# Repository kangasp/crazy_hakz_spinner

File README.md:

# crazy_hakz_spinner
Spinning LEDs

### Notes from 2-24-23
--------------------------------------------
The footprint for the through beam sensor is wrong - pins 3 and 4 should be switched.
Pin 4 is actually ground / emiter, and pin 3 is actually the collector / vcc.

The through beem should sensor should not be pulled up to VCC - which is 5v.  It should 
be pulled up to 3.3v.

The level shifter should be moved - as it's too close to the mounting bracket... maybe get a bigger one.

Consider moving the positional / counter through beam to the edge.

Consider adding a testpoint header.

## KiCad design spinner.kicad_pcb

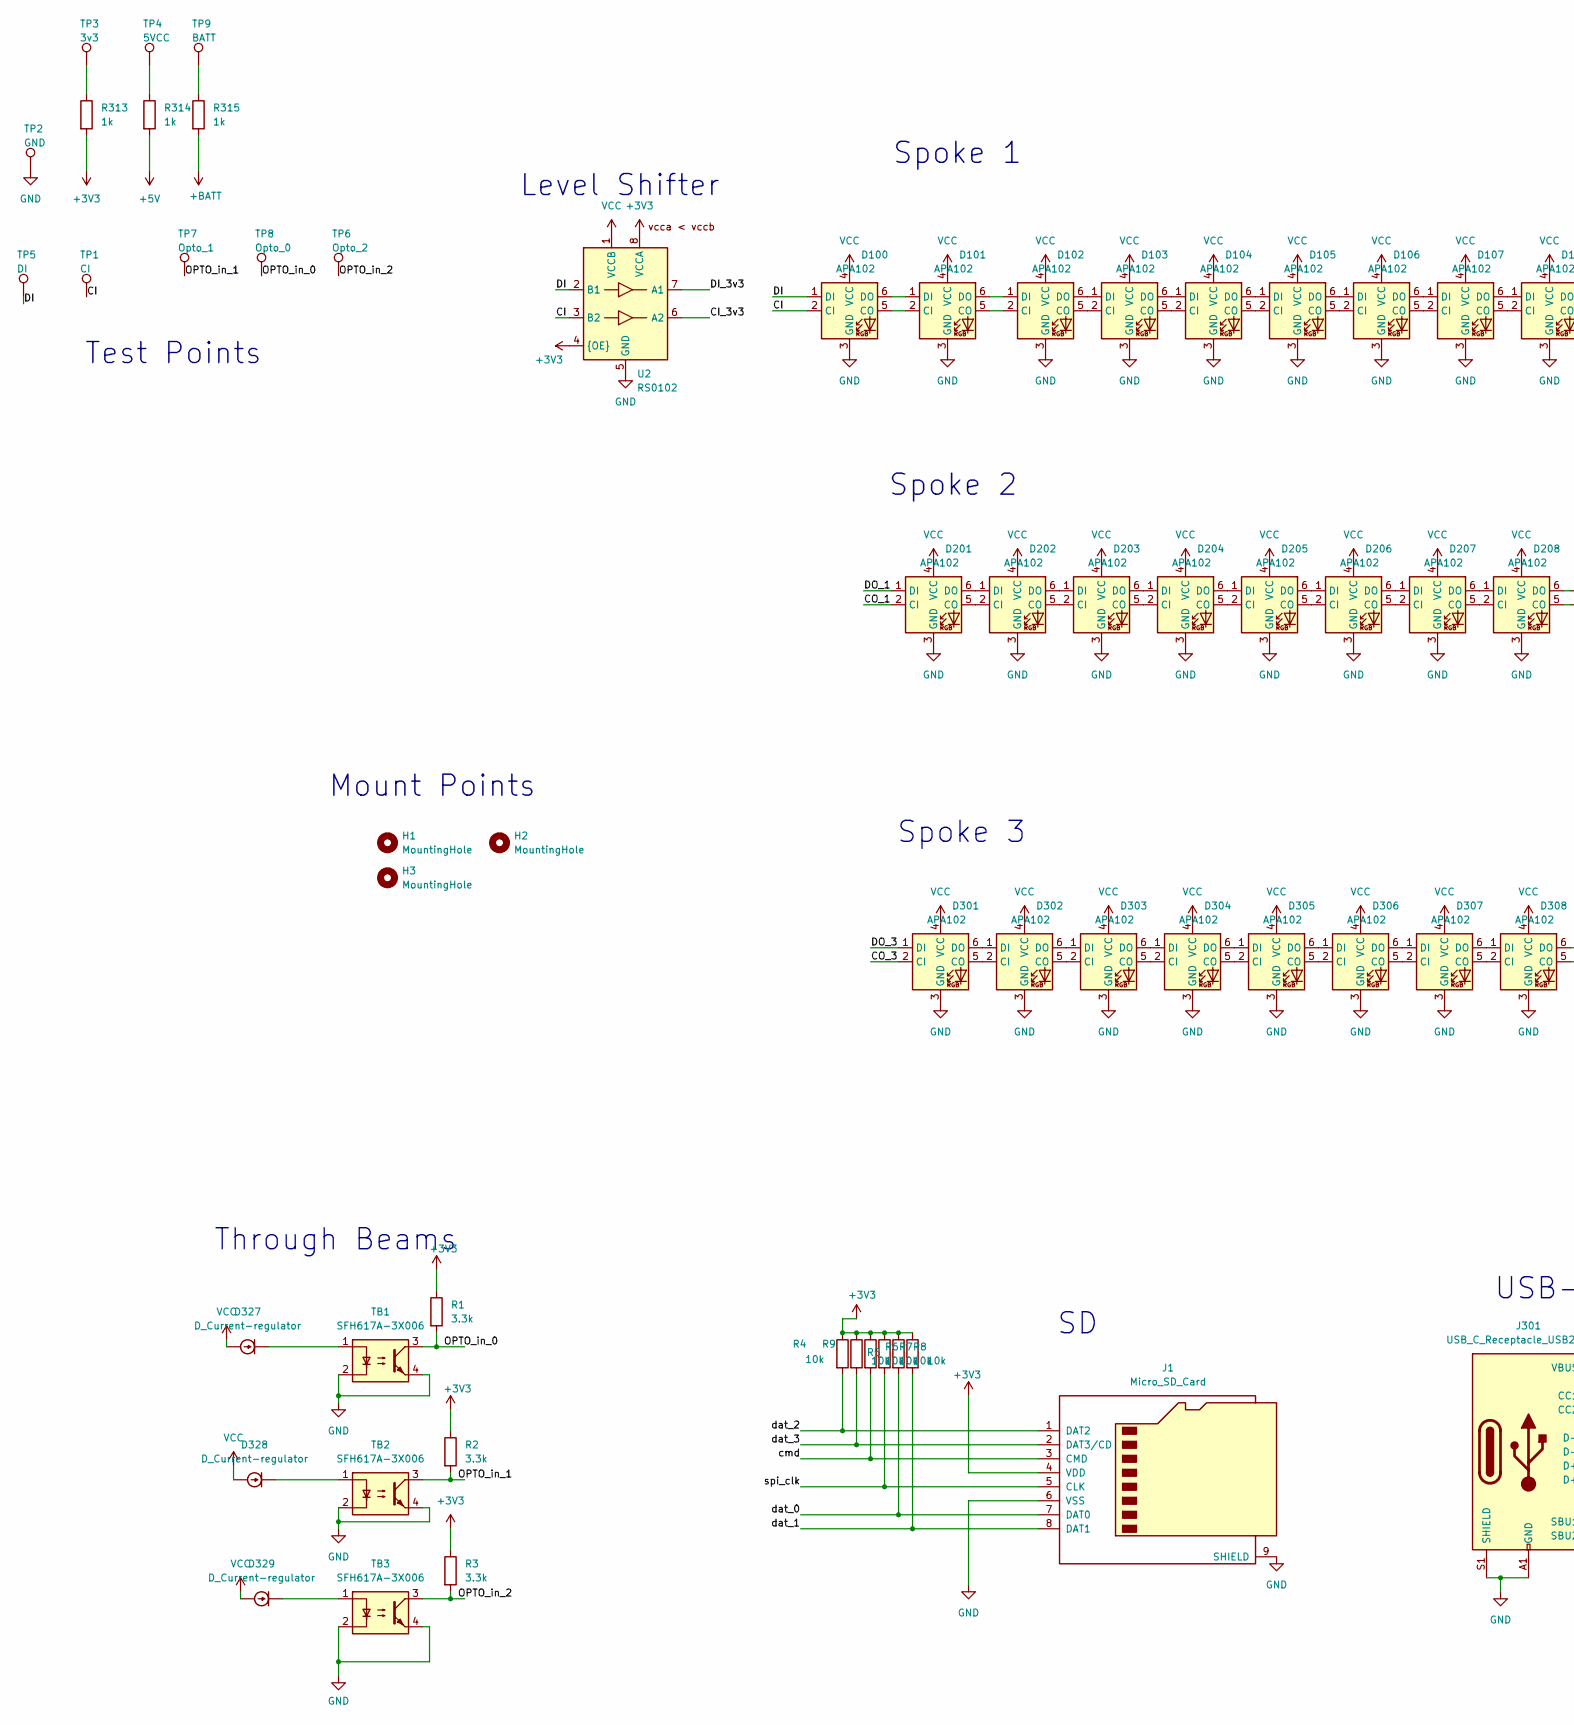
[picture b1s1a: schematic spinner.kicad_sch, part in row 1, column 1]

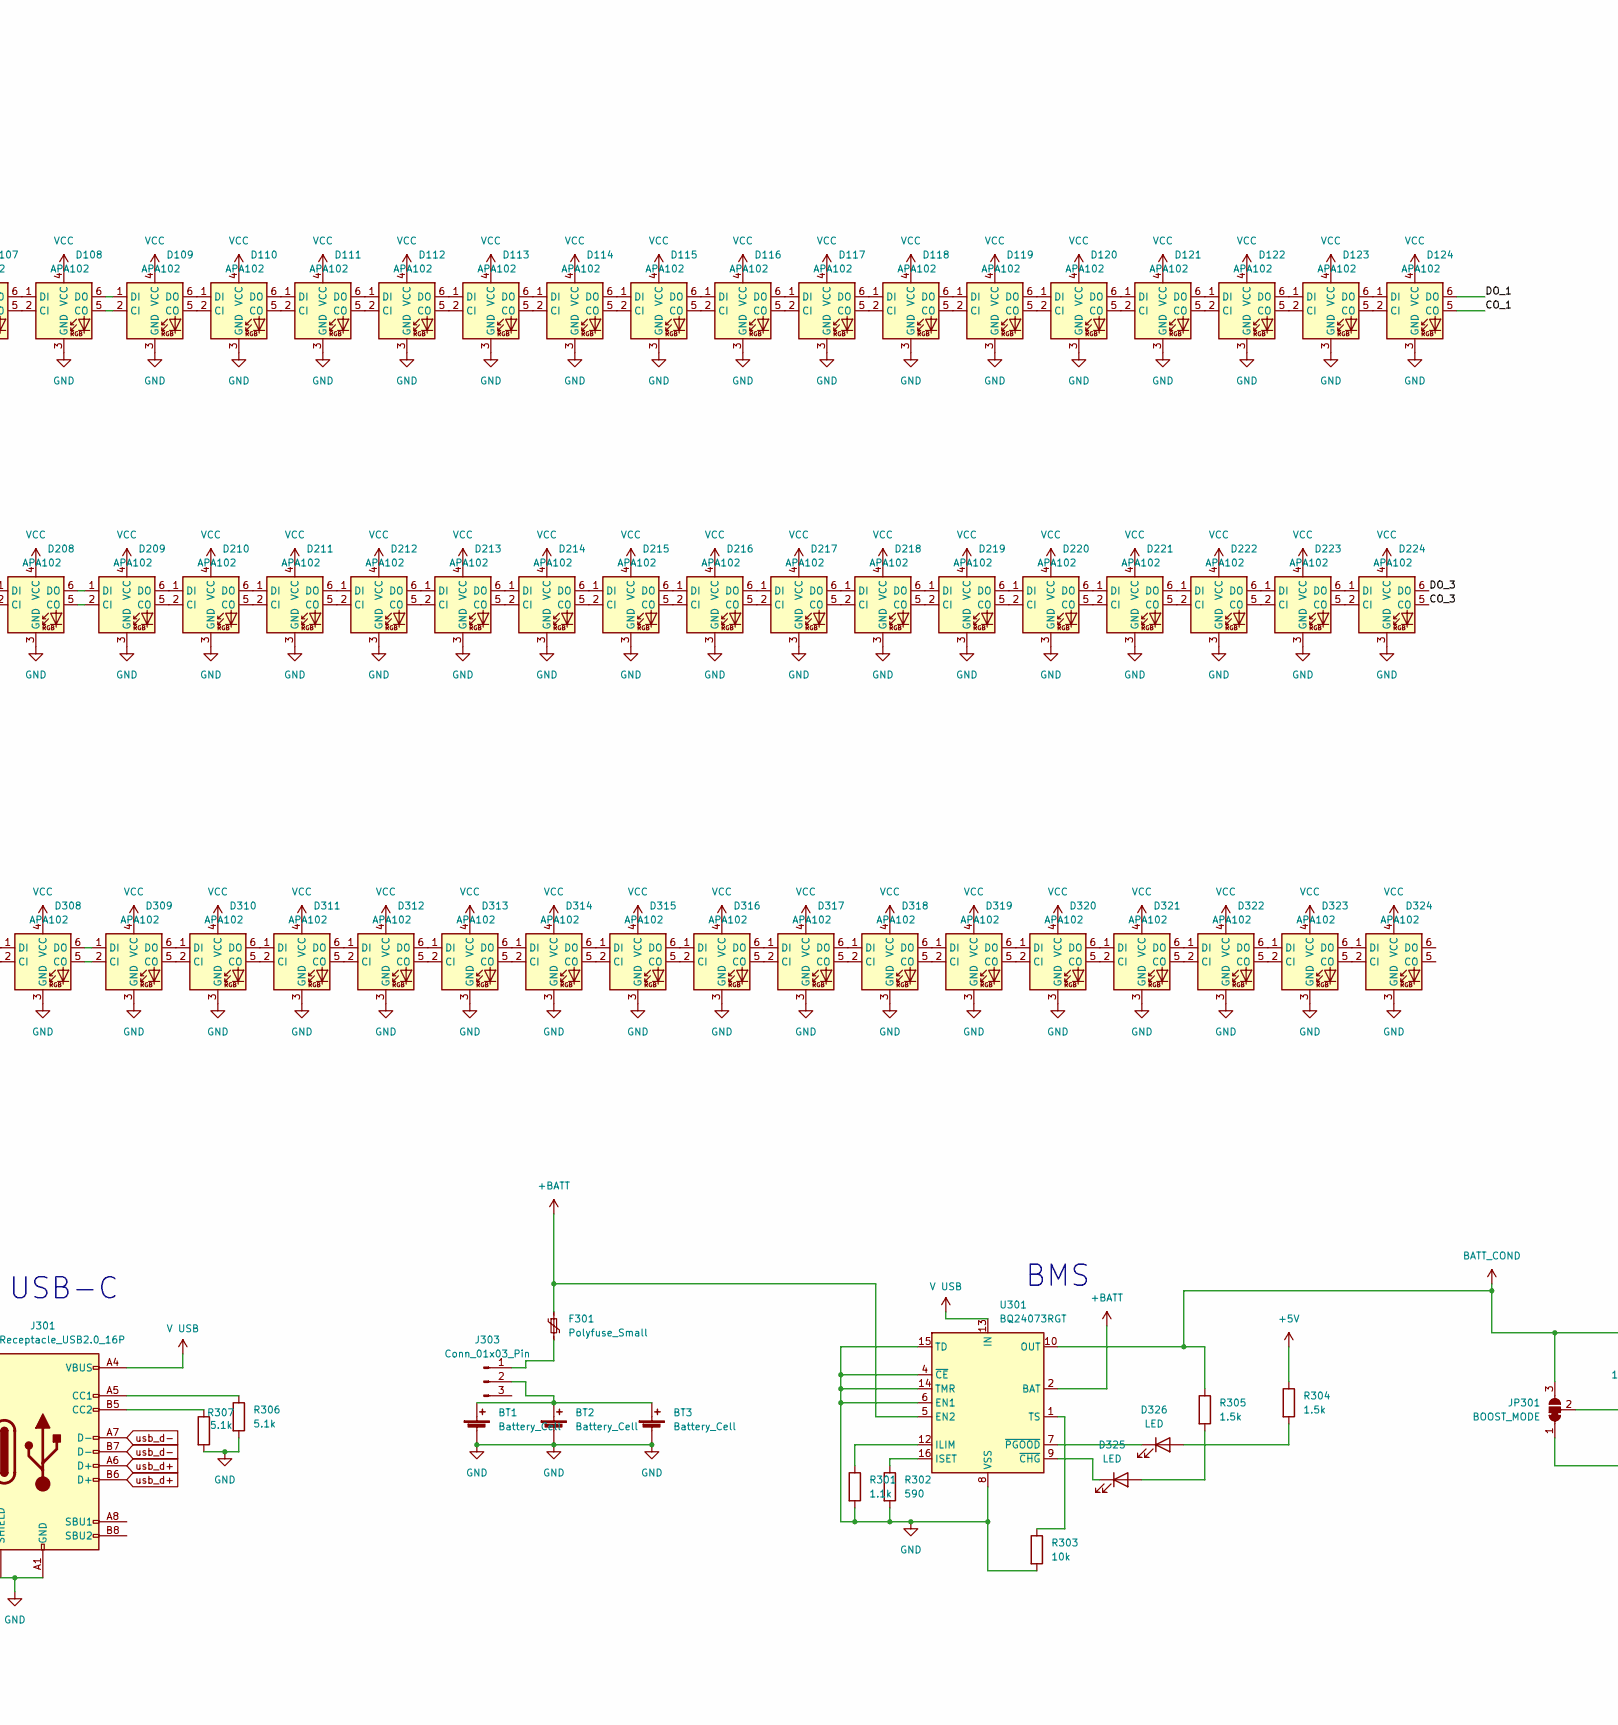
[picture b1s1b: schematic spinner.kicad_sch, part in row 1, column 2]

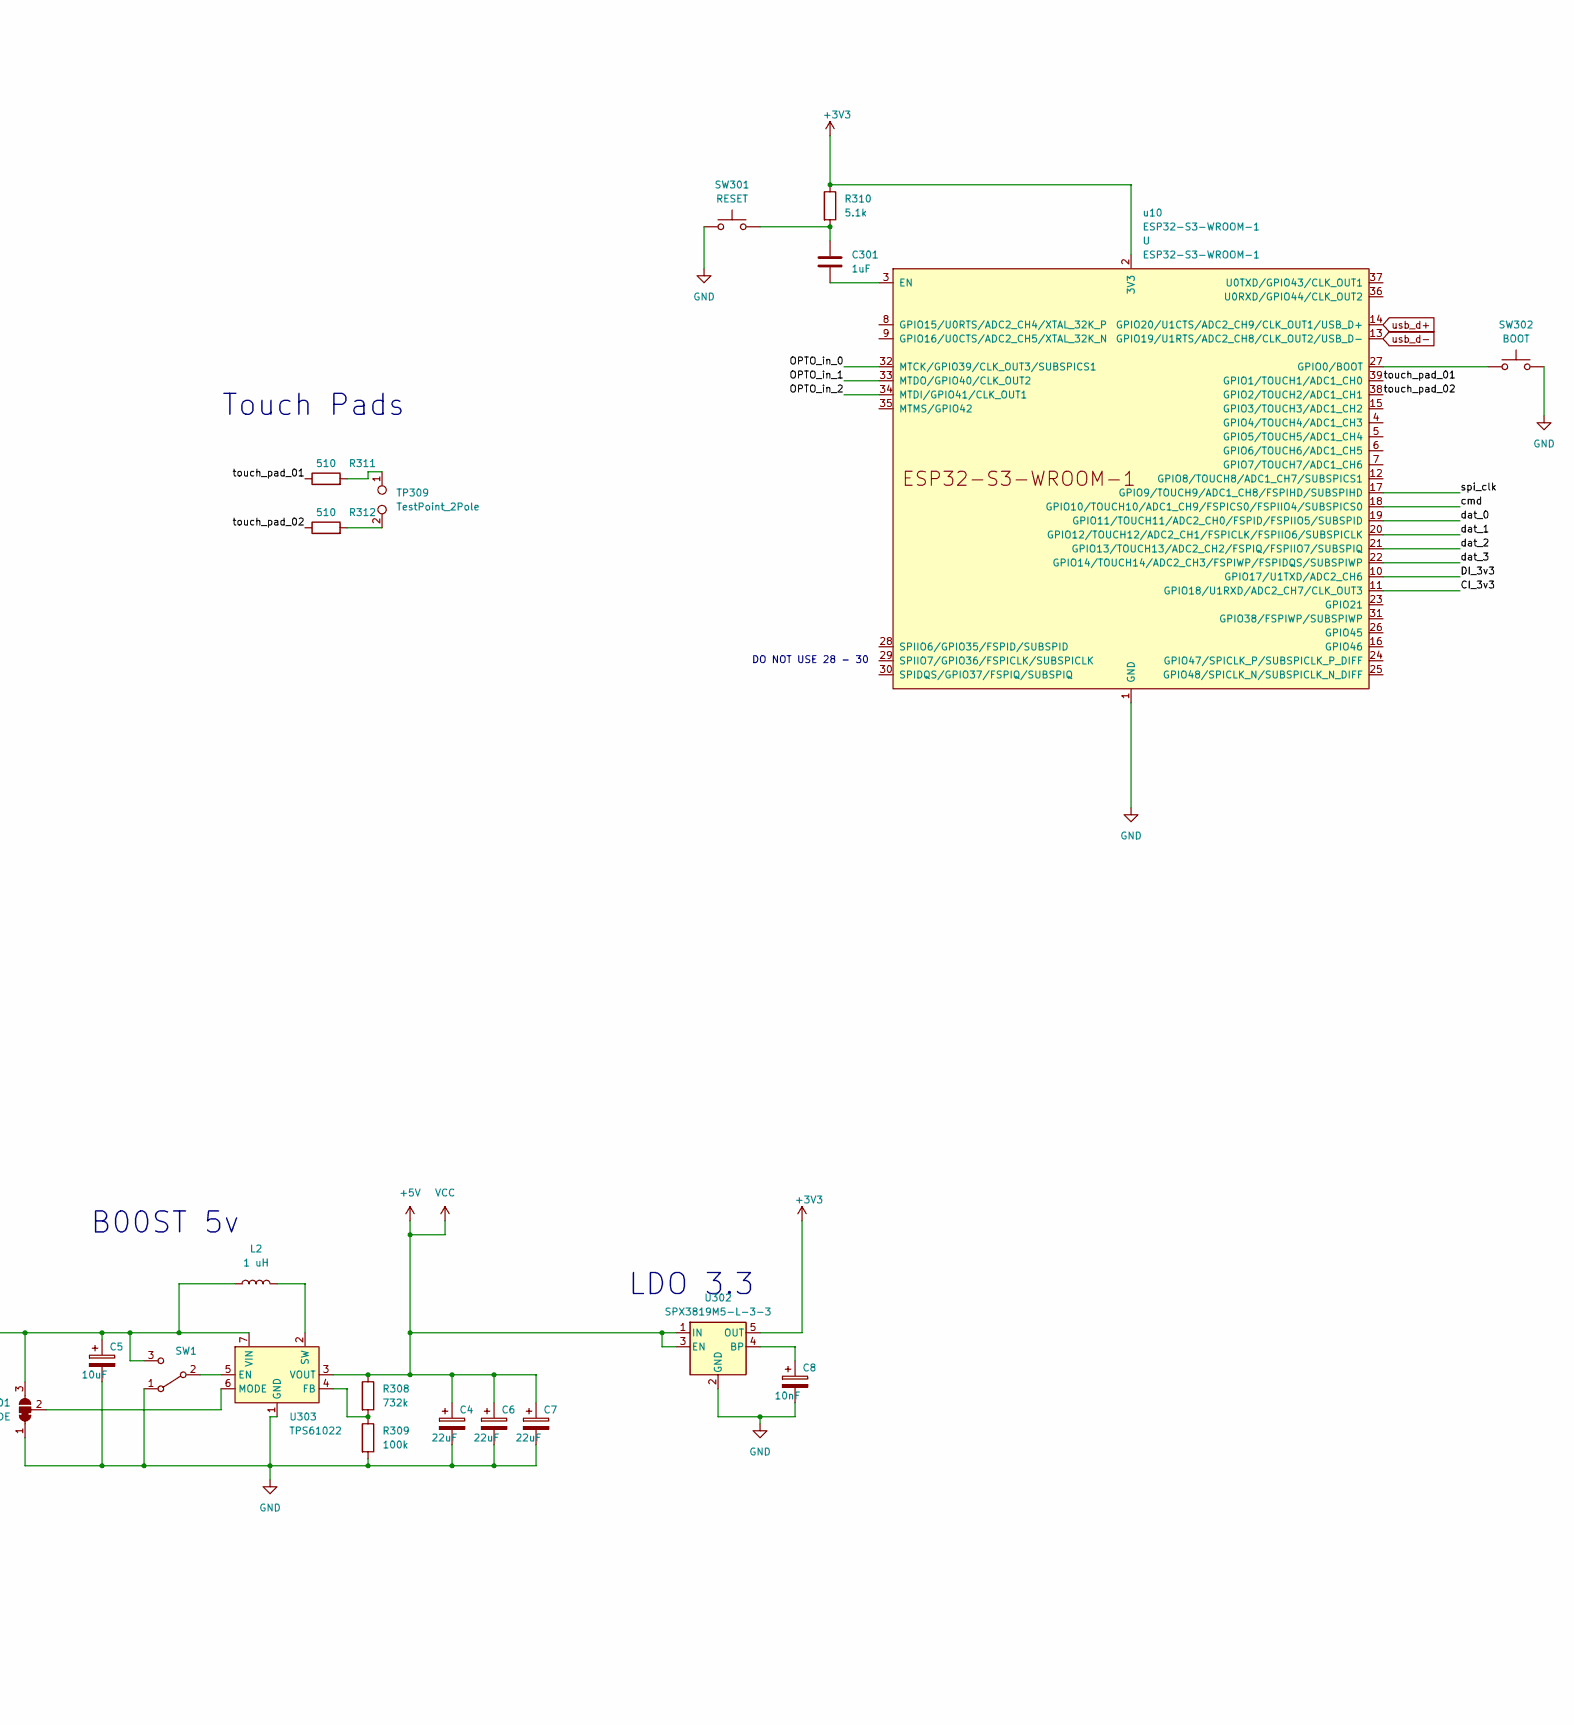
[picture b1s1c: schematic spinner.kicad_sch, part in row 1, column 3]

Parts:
BT1, BT2, BT3: Battery_Cell; Spinner_BatteryHolder_Keystone_2460_1xAA
C4, C6, C7: 22uF; C_0805_2012Metric_Pad1.18x1.45mm_HandSolder
C5: 10uF; C_0805_2012Metric_Pad1.18x1.45mm_HandSolder
C8: 10nF; C_0805_2012Metric
C301: 1uF; C_0805_2012Metric_Pad1.18x1.45mm_HandSolder
D100, D101, D102, D103, D104, D105, D106, D107, D108, D109, D110, D111, D112, D113, D114, D115, D116, D117, D118, D119, D120, D121, D122, D123, D124, D201, D202, D203, D204, D205, D206, D207, D208, D209, D210, D211, D212, D213, D214, D215, D216, D217, D218, D219, D220, D221, D222, D223, D224, D301, D302, D303, D304, D305, D306, D307, D308, D309, D310, D311, D312, D313, D314, D315, D316, D317, D318, D319, D320, D321, D322, D323, D324: APA102; SK9822-hakz
D325, D326: LED; LED_0805_2012Metric
D327, D328, D329: D_Current-regulator; D_SOD-123
F301: Polyfuse_Small; R_1210_3225Metric
H1, H2, H3: MountingHole; MountingHole_3mm
J1: Micro_SD_Card; microSD_HC_Hirose_DM3AT-SF-PEJM5
J301: USB_C_Receptacle_USB2.0_16P; USB_C_Receptacle_GCT_USB4105-xx-A_16P_TopMnt_Horizontal
J303: Conn_01x03_Pin; PinHeader_1x03_P2.54mm_HRZ_SMD_Pin1Left
JP301: BOOST_MODE; SolderJumper-3_P1.3mm_Bridged12_RoundedPad1.0x1.5mm
L2: 1 uH; L_Coilcraft_XAL7030-102
R1, R2, R3: 3.3k; R_0805_2012Metric_Pad1.20x1.40mm_HandSolder
R4, R5, R6, R7, R8, R9, R303: 10k; R_0805_2012Metric_Pad1.20x1.40mm_HandSolder
R301: 1.1k; R_0805_2012Metric_Pad1.20x1.40mm_HandSolder
R302: 590; R_0805_2012Metric_Pad1.20x1.40mm_HandSolder
R304, R305: 1.5k; R_0805_2012Metric_Pad1.20x1.40mm_HandSolder
R306, R307, R310: 5.1k; R_0603_1608Metric
R308: 732k; R_0805_2012Metric
R309: 100k; R_0805_2012Metric
R311, R312: 510; R_0603_1608Metric
R313, R314, R315: 1k; R_0603_1608Metric
SW1: SW_SPDT; SW_SPDT_CK-JS102011SAQN
SW301: RESET; SW_Push_SPST_NO_Alps_SKRK
SW302: BOOT; SW_Push_SPST_NO_Alps_SKRK
TB1, TB2, TB3: SFH617A-3X006; MULTI_PART_THRU_BEAM
TP1: CI; TestPoint_Pad_D2.5mm
TP2: GND; TestPoint_Pad_D2.5mm
TP3: 3v3; TestPoint_Pad_D2.5mm
TP4: 5VCC; TestPoint_Pad_D2.5mm
TP5: DI; TestPoint_Pad_D2.5mm
TP6: Opto_2; TestPoint_Pad_D2.5mm
TP7: Opto_1; TestPoint_Pad_D2.5mm
TP8: Opto_0; TestPoint_Pad_D2.5mm
TP9: BATT; TestPoint_Pad_D2.5mm
TP309: TestPoint_2Pole; TouchSlider-2_20x10mm
U2: RS0102; MSOP-8_3x3mm_P0.65mm
U301: BQ24073RGT; VQFN-16-1EP_3x3mm_P0.5mm_EP1.6x1.6mm
U302: SPX3819M5-L-3-3; SOT-23-5
U303: TPS61022; Texas_RWU0007A_VQFN-7_2x2mm_P0.5mm
u10: ESP32-S3-WROOM-1

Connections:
+3V3: J1.4 (VDD), R1.1, R2.1, R3.1, R4.1, R5.1, R6.1, R7.1, R8.1, R9.1, R310.1, R313.2, U2.4 ({OE}), U2.8 (VCCA), U302.5 (OUT), u10.2 (3V3)
+5V: C4.1, C6.1, C7.1, D100.4 (VCC), D101.4 (VCC), D102.4 (VCC), D103.4 (VCC), D104.4 (VCC), D105.4 (VCC), D106.4 (VCC), D107.4 (VCC), D108.4 (VCC), D109.4 (VCC), D110.4 (VCC), D111.4 (VCC), D112.4 (VCC), D113.4 (VCC), D114.4 (VCC), D115.4 (VCC), D116.4 (VCC), D117.4 (VCC), D118.4 (VCC), D119.4 (VCC), D120.4 (VCC), D121.4 (VCC), D122.4 (VCC), D123.4 (VCC), D124.4 (VCC), D201.4 (VCC), D202.4 (VCC), D203.4 (VCC), D204.4 (VCC), D205.4 (VCC), D206.4 (VCC), D207.4 (VCC), D208.4 (VCC), D209.4 (VCC), D210.4 (VCC), D211.4 (VCC), D212.4 (VCC), D213.4 (VCC), D214.4 (VCC), D215.4 (VCC), D216.4 (VCC), D217.4 (VCC), D218.4 (VCC), D219.4 (VCC), D220.4 (VCC), D221.4 (VCC), D222.4 (VCC), D223.4 (VCC), D224.4 (VCC), D301.4 (VCC), D302.4 (VCC), D303.4 (VCC), D304.4 (VCC), D305.4 (VCC), D306.4 (VCC), D307.4 (VCC), D308.4 (VCC), D309.4 (VCC), D310.4 (VCC), D311.4 (VCC), D312.4 (VCC), D313.4 (VCC), D314.4 (VCC), D315.4 (VCC), D316.4 (VCC), D317.4 (VCC), D318.4 (VCC), D319.4 (VCC), D320.4 (VCC), D321.4 (VCC), D322.4 (VCC), D323.4 (VCC), D324.4 (VCC), D327.2 (A), D328.2 (A), D329.2 (A), R304.1, R308.1, R314.2, U2.1 (VCCB), U302.1 (IN), U302.3 (EN), U303.3 (VOUT)
+BATT: F301.1, R315.2, U301.2 (BAT), U301.3 (BAT), U301.5 (EN2)
/CI: D100.2 (CI), TP1.1, U2.3 (B2)
/CI_3v3: U2.6 (A2), u10.11 (GPIO18/U1RXD/ADC2_CH7/CLK_OUT3)
/CO_1: D124.5 (CO), D201.2 (CI)
/CO_3: D224.5 (CO), D301.2 (CI)
/DI: D100.1 (DI), TP5.1, U2.2 (B1)
/DI_3v3: U2.7 (A1), u10.10 (GPIO17/U1TXD/ADC2_CH6)
/DO_1: D124.6 (DO), D201.1 (DI)
/DO_3: D224.6 (DO), D301.1 (DI)
/OPTO_in_0: R1.2, TB1.3, TP8.1, u10.32 (MTCK/GPIO39/CLK_OUT3/SUBSPICS1)
/OPTO_in_1: R2.2, TB2.3, TP7.1, u10.33 (MTDO/GPIO40/CLK_OUT2)
/OPTO_in_2: R3.2, TB3.3, TP6.1, u10.34 (MTDI/GPIO41/CLK_OUT1)
/cmd: J1.3 (CMD), R6.2, u10.18 (GPIO10/TOUCH10/ADC1_CH9/FSPICS0/FSPIIO4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)
/dat_0: J1.7 (DAT0), R8.2, u10.19 (GPIO11/TOUCH11/ADC2_CH0/FSPID/FSPIIO5/S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)
/dat_1: J1.8 (DAT1), R9.2, u10.20 (GPIO12/TOUCH12/ADC2_CH1/FSPICLK/FSPIIO6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)
/dat_2: J1.1 (DAT2), R4.2, u10.21 (GPIO13/TOUCH13/ADC2_CH2/FSPIQ/FSPIIO7/S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)
/dat_3: J1.2 (DAT3/CD), R5.2, u10.22 (GPIO14/TOUCH14/ADC2_CH3/FSPIWP/FSPIDQS/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)
/spi_clk: J1.5 (CLK), R7.2, u10.17 (GPIO9/TOUCH9/ADC1_CH8/FSPIHD/SUBSPIHD)
/touch_pad_01: R311.1, u10.39 (GPIO1/TOUCH1/ADC1_CH0)
/touch_pad_02: R312.1, u10.38 (GPIO2/TOUCH2/ADC1_CH1)
BATT_COND: C5.1, JP301.3 (B), L2.1, R305.1, SW1.3 (C), U301.10 (OUT), U301.11 (OUT), U303.7 (VIN)
GND: BT1.2 (-), BT2.2 (-), BT3.2 (-), C4.2, C5.2, C6.2, C7.2, C8.2, D100.3 (GND), D101.3 (GND), D102.3 (GND), D103.3 (GND), D104.3 (GND), D105.3 (GND), D106.3 (GND), D107.3 (GND), D108.3 (GND), D109.3 (GND), D110.3 (GND), D111.3 (GND), D112.3 (GND), D113.3 (GND), D114.3 (GND), D115.3 (GND), D116.3 (GND), D117.3 (GND), D118.3 (GND), D119.3 (GND), D120.3 (GND), D121.3 (GND), D122.3 (GND), D123.3 (GND), D124.3 (GND), D201.3 (GND), D202.3 (GND), D203.3 (GND), D204.3 (GND), D205.3 (GND), D206.3 (GND), D207.3 (GND), D208.3 (GND), D209.3 (GND), D210.3 (GND), D211.3 (GND), D212.3 (GND), D213.3 (GND), D214.3 (GND), D215.3 (GND), D216.3 (GND), D217.3 (GND), D218.3 (GND), D219.3 (GND), D220.3 (GND), D221.3 (GND), D222.3 (GND), D223.3 (GND), D224.3 (GND), D301.3 (GND), D302.3 (GND), D303.3 (GND), D304.3 (GND), D305.3 (GND), D306.3 (GND), D307.3 (GND), D308.3 (GND), D309.3 (GND), D310.3 (GND), D311.3 (GND), D312.3 (GND), D313.3 (GND), D314.3 (GND), D315.3 (GND), D316.3 (GND), D317.3 (GND), D318.3 (GND), D319.3 (GND), D320.3 (GND), D321.3 (GND), D322.3 (GND), D323.3 (GND), D324.3 (GND), J1.6 (VSS), J1.9 (SHIELD), J301.A1 (GND), J301.A12 (GND), J301.B1 (GND), J301.B12 (GND), J301.S1 (SHIELD), JP301.1 (A), R301.2, R302.2, R303.2, R306.2, R307.2, R309.2, SW1.1 (A), SW301.1, SW302.2, TB1.2, TB1.4, TB2.2, TB2.4, TB3.2, TB3.4, TP2.1, U2.5 (GND), U301.4 (~CE), U301.6 (EN1), U301.8 (VSS), U301.14 (TMR), U301.15 (TD), U301.17 (VSS), U302.2 (GND), U303.1 (GND), u10.1 (GND), u10.40 (GND), u10.41 (GND)
unnamed: BT1.1 (+), BT2.1 (+), BT3.1 (+), J303.2
unnamed: C301.1, R310.2, SW301.2
unnamed: D100.5 (CO), D101.2 (CI)
unnamed: D100.6 (DO), D101.1 (DI)
unnamed: D101.5 (CO), D102.2 (CI)
unnamed: D101.6 (DO), D102.1 (DI)
unnamed: D102.5 (CO), D103.2 (CI)
unnamed: D102.6 (DO), D103.1 (DI)
unnamed: D103.5 (CO), D104.2 (CI)
unnamed: D103.6 (DO), D104.1 (DI)
unnamed: D104.5 (CO), D105.2 (CI)
unnamed: D104.6 (DO), D105.1 (DI)
unnamed: D105.5 (CO), D106.2 (CI)
unnamed: D105.6 (DO), D106.1 (DI)
unnamed: D106.5 (CO), D107.2 (CI)
unnamed: D106.6 (DO), D107.1 (DI)
unnamed: D107.5 (CO), D108.2 (CI)
unnamed: D107.6 (DO), D108.1 (DI)
unnamed: D108.5 (CO), D109.2 (CI)
unnamed: D108.6 (DO), D109.1 (DI)
unnamed: D109.5 (CO), D110.2 (CI)
unnamed: D109.6 (DO), D110.1 (DI)
unnamed: D110.5 (CO), D111.2 (CI)
unnamed: D110.6 (DO), D111.1 (DI)
unnamed: D111.5 (CO), D112.2 (CI)
unnamed: D111.6 (DO), D112.1 (DI)
unnamed: D112.5 (CO), D113.2 (CI)
unnamed: D112.6 (DO), D113.1 (DI)
unnamed: D113.5 (CO), D114.2 (CI)
unnamed: D113.6 (DO), D114.1 (DI)
unnamed: D114.5 (CO), D115.2 (CI)
unnamed: D114.6 (DO), D115.1 (DI)
unnamed: D115.5 (CO), D116.2 (CI)
unnamed: D115.6 (DO), D116.1 (DI)
unnamed: D116.5 (CO), D117.2 (CI)
unnamed: D116.6 (DO), D117.1 (DI)
unnamed: D117.5 (CO), D118.2 (CI)
unnamed: D117.6 (DO), D118.1 (DI)
unnamed: D118.5 (CO), D119.2 (CI)
unnamed: D118.6 (DO), D119.1 (DI)
unnamed: D119.5 (CO), D120.2 (CI)
unnamed: D119.6 (DO), D120.1 (DI)
unnamed: D120.5 (CO), D121.2 (CI)
unnamed: D120.6 (DO), D121.1 (DI)
unnamed: D121.5 (CO), D122.2 (CI)
unnamed: D121.6 (DO), D122.1 (DI)
unnamed: D122.5 (CO), D123.2 (CI)
unnamed: D122.6 (DO), D123.1 (DI)
unnamed: D123.5 (CO), D124.2 (CI)
unnamed: D123.6 (DO), D124.1 (DI)
unnamed: D201.5 (CO), D202.2 (CI)
unnamed: D201.6 (DO), D202.1 (DI)
unnamed: D202.5 (CO), D203.2 (CI)
unnamed: D202.6 (DO), D203.1 (DI)
unnamed: D203.5 (CO), D204.2 (CI)
unnamed: D203.6 (DO), D204.1 (DI)
unnamed: D204.5 (CO), D205.2 (CI)
unnamed: D204.6 (DO), D205.1 (DI)
unnamed: D205.5 (CO), D206.2 (CI)
unnamed: D205.6 (DO), D206.1 (DI)
unnamed: D206.5 (CO), D207.2 (CI)
unnamed: D206.6 (DO), D207.1 (DI)
unnamed: D207.5 (CO), D208.2 (CI)
unnamed: D207.6 (DO), D208.1 (DI)
unnamed: D208.5 (CO), D209.2 (CI)
unnamed: D208.6 (DO), D209.1 (DI)
unnamed: D209.5 (CO), D210.2 (CI)
unnamed: D209.6 (DO), D210.1 (DI)
unnamed: D210.5 (CO), D211.2 (CI)
unnamed: D210.6 (DO), D211.1 (DI)
unnamed: D211.5 (CO), D212.2 (CI)
unnamed: D211.6 (DO), D212.1 (DI)
unnamed: D212.5 (CO), D213.2 (CI)
unnamed: D212.6 (DO), D213.1 (DI)
unnamed: D213.5 (CO), D214.2 (CI)
unnamed: D213.6 (DO), D214.1 (DI)
unnamed: D214.5 (CO), D215.2 (CI)
unnamed: D214.6 (DO), D215.1 (DI)
unnamed: D215.5 (CO), D216.2 (CI)
unnamed: D215.6 (DO), D216.1 (DI)
unnamed: D216.5 (CO), D217.2 (CI)
unnamed: D216.6 (DO), D217.1 (DI)
unnamed: D217.5 (CO), D218.2 (CI)
unnamed: D217.6 (DO), D218.1 (DI)
unnamed: D218.5 (CO), D219.2 (CI)
unnamed: D218.6 (DO), D219.1 (DI)
unnamed: D219.5 (CO), D220.2 (CI)
unnamed: D219.6 (DO), D220.1 (DI)
unnamed: D220.5 (CO), D221.2 (CI)
unnamed: D220.6 (DO), D221.1 (DI)
unnamed: D221.5 (CO), D222.2 (CI)
unnamed: D221.6 (DO), D222.1 (DI)
unnamed: D222.5 (CO), D223.2 (CI)
unnamed: D222.6 (DO), D223.1 (DI)
unnamed: D223.5 (CO), D224.2 (CI)
unnamed: D223.6 (DO), D224.1 (DI)
unnamed: D301.5 (CO), D302.2 (CI)
unnamed: D301.6 (DO), D302.1 (DI)
unnamed: D302.5 (CO), D303.2 (CI)
unnamed: D302.6 (DO), D303.1 (DI)
unnamed: D303.5 (CO), D304.2 (CI)
unnamed: D303.6 (DO), D304.1 (DI)
unnamed: D304.5 (CO), D305.2 (CI)
unnamed: D304.6 (DO), D305.1 (DI)
unnamed: D305.5 (CO), D306.2 (CI)
unnamed: D305.6 (DO), D306.1 (DI)
unnamed: D306.5 (CO), D307.2 (CI)
unnamed: D306.6 (DO), D307.1 (DI)
unnamed: D307.5 (CO), D308.2 (CI)
unnamed: D307.6 (DO), D308.1 (DI)
unnamed: D308.5 (CO), D309.2 (CI)
unnamed: D308.6 (DO), D309.1 (DI)
unnamed: D309.5 (CO), D310.2 (CI)
unnamed: D309.6 (DO), D310.1 (DI)
unnamed: D310.5 (CO), D311.2 (CI)
unnamed: D310.6 (DO), D311.1 (DI)
unnamed: D311.5 (CO), D312.2 (CI)
unnamed: D311.6 (DO), D312.1 (DI)
unnamed: D312.5 (CO), D313.2 (CI)
unnamed: D312.6 (DO), D313.1 (DI)
unnamed: D313.5 (CO), D314.2 (CI)
unnamed: D313.6 (DO), D314.1 (DI)
unnamed: D314.5 (CO), D315.2 (CI)
unnamed: D314.6 (DO), D315.1 (DI)
unnamed: D315.5 (CO), D316.2 (CI)
unnamed: D315.6 (DO), D316.1 (DI)
unnamed: D316.5 (CO), D317.2 (CI)
unnamed: D316.6 (DO), D317.1 (DI)
unnamed: D317.5 (CO), D318.2 (CI)
unnamed: D317.6 (DO), D318.1 (DI)
unnamed: D318.5 (CO), D319.2 (CI)
unnamed: D318.6 (DO), D319.1 (DI)
unnamed: D319.5 (CO), D320.2 (CI)
unnamed: D319.6 (DO), D320.1 (DI)
unnamed: D320.5 (CO), D321.2 (CI)
unnamed: D320.6 (DO), D321.1 (DI)
unnamed: D321.5 (CO), D322.2 (CI)
unnamed: D321.6 (DO), D322.1 (DI)
unnamed: D322.5 (CO), D323.2 (CI)
unnamed: D322.6 (DO), D323.1 (DI)
unnamed: D323.5 (CO), D324.2 (CI)
unnamed: D323.6 (DO), D324.1 (DI)
unnamed: D325.2 (A), R305.2
unnamed: D325.1 (K), U301.9 (~CHG)
unnamed: D326.2 (A), R304.2
unnamed: D326.1 (K), U301.7 (~PGOOD)
unnamed: D327.1 (K), TB1.1
unnamed: D328.1 (K), TB2.1
unnamed: D329.1 (K), TB3.1
unnamed: J301.A5 (CC1), R306.1
unnamed: J301.B5 (CC2), R307.1
unnamed: F301.2, J303.1
unnamed: JP301.2 (C), U303.6 (MODE)
unnamed: R311.2, TP309.1
unnamed: R312.2, TP309.2
unnamed: R313.1, TP3.1
unnamed: R314.1, TP4.1
unnamed: R315.1, TP9.1
unnamed: SW1.2 (B), U303.5 (EN)
unnamed: R301.1, U301.12 (ILIM)
unnamed: R302.1, U301.16 (ISET)
unnamed: R303.1, U301.1 (TS)
unnamed: C8.1, U302.4 (BP)
unnamed: R308.2, R309.1, U303.4 (FB)
unnamed: L2.2, U303.2 (SW)
unnamed: C301.2, u10.3 (EN)
unnamed: SW302.1, u10.27 (GPIO0/BOOT)
V USB: J301.A4 (VBUS), J301.A9 (VBUS), J301.B4 (VBUS), J301.B9 (VBUS), U301.13 (IN)
usb_d+: J301.A6 (D+), J301.B6 (D+), u10.14 (GPIO20/U1CTS/ADC2_CH9/CLK_OUT1/USB_D+)
usb_d-: J301.A7 (D-), J301.B7 (D-), u10.13 (GPIO19/U1RTS/ADC2_CH8/CLK_OUT2/USB_D-)

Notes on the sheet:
Mount Points
B00ST 5v
Test Points
DO NOT USE 28 - 30
Through Beams
Level Shifter
Spoke 1
Spoke 3
USB-C
BMS
Touch Pads
LDO 3.3
Spoke 2

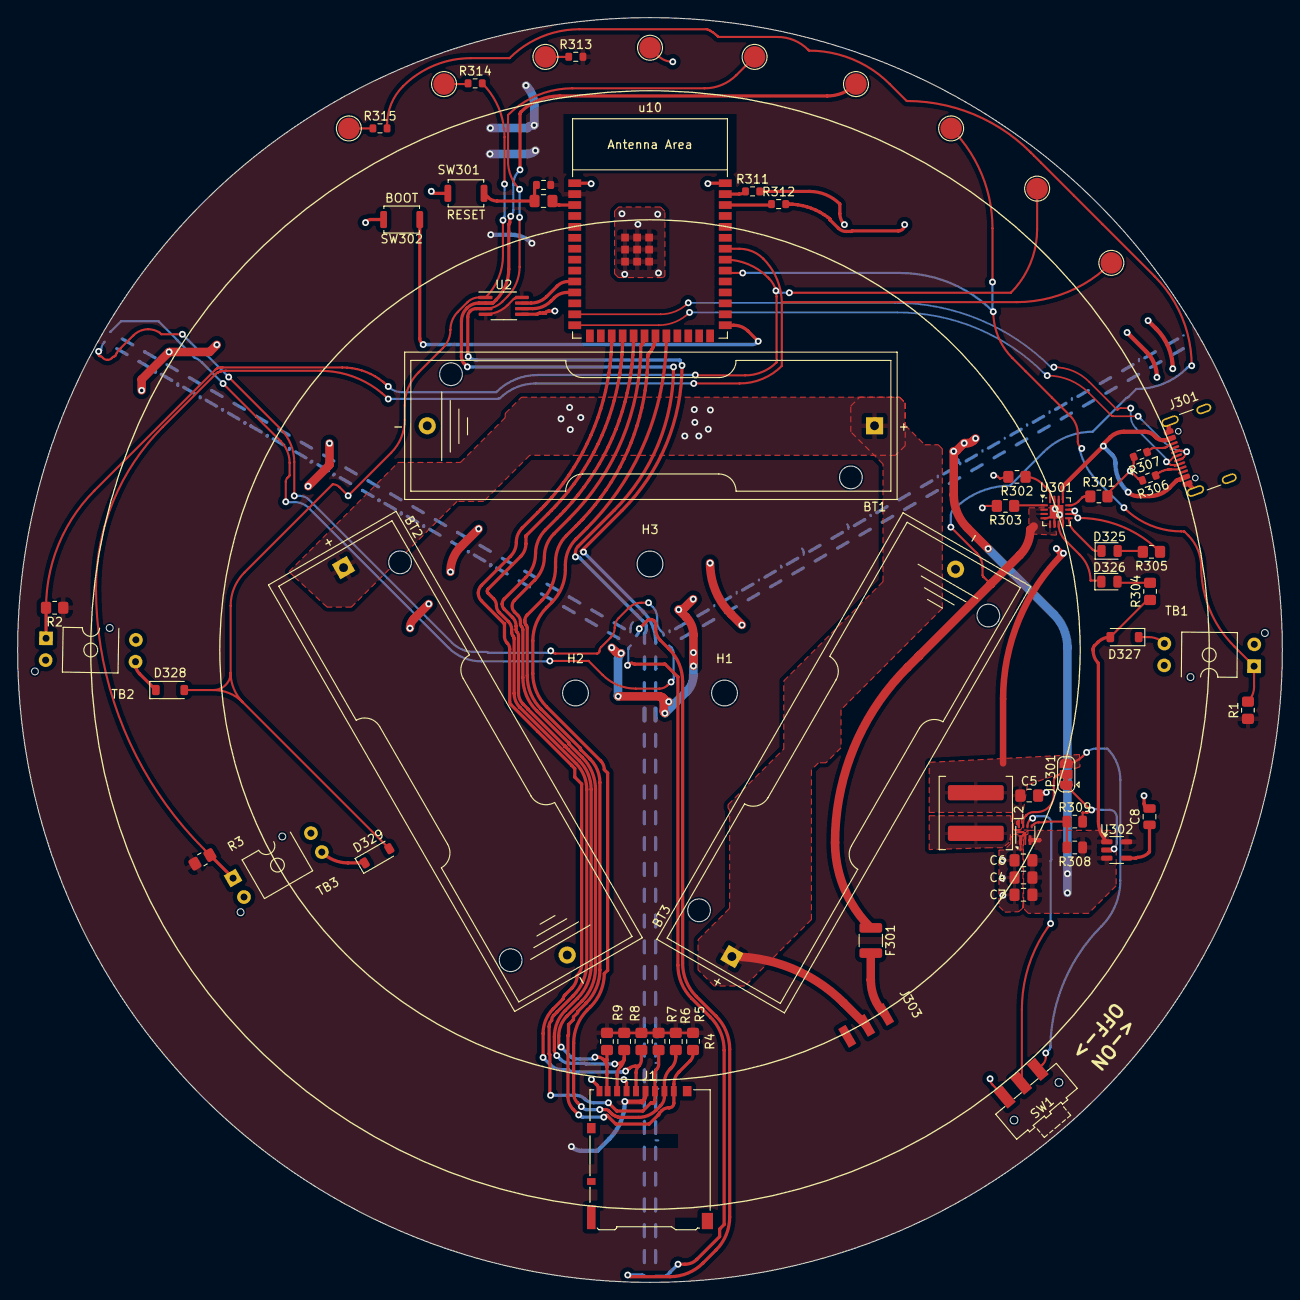
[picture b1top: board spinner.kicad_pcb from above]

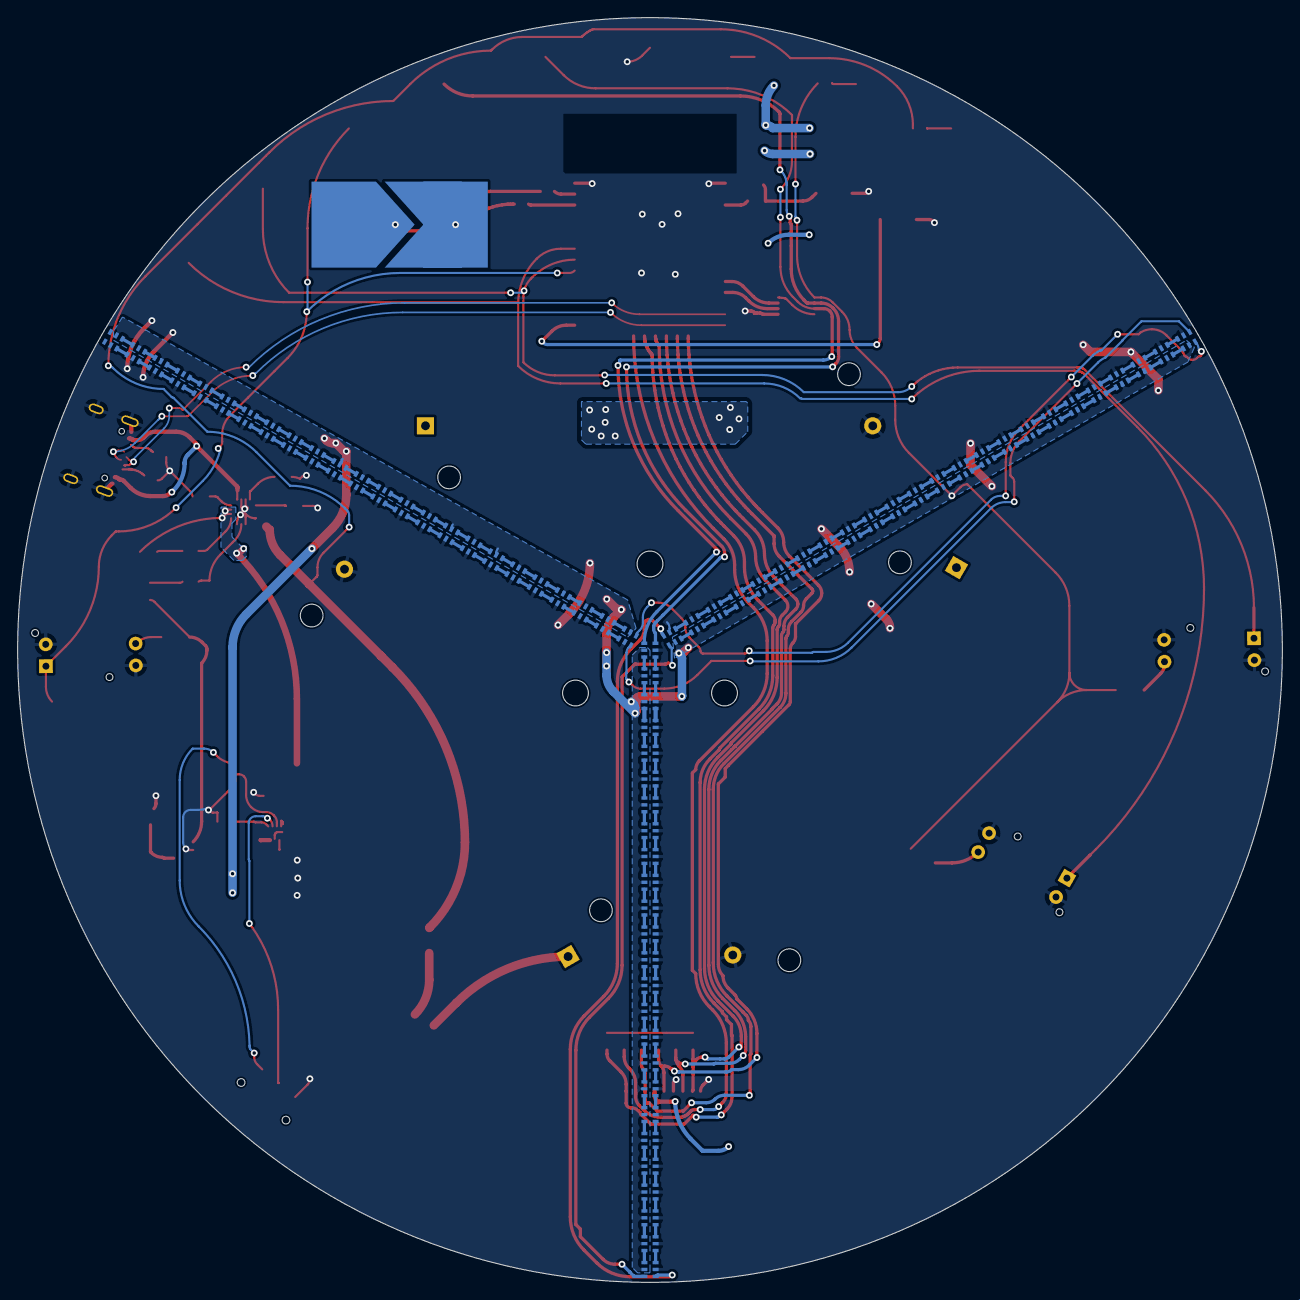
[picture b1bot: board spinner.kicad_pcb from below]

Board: 2 copper layers, 147.0 x 147.0 mm, 141 parts (74 on the bottom side), 194 nets.
